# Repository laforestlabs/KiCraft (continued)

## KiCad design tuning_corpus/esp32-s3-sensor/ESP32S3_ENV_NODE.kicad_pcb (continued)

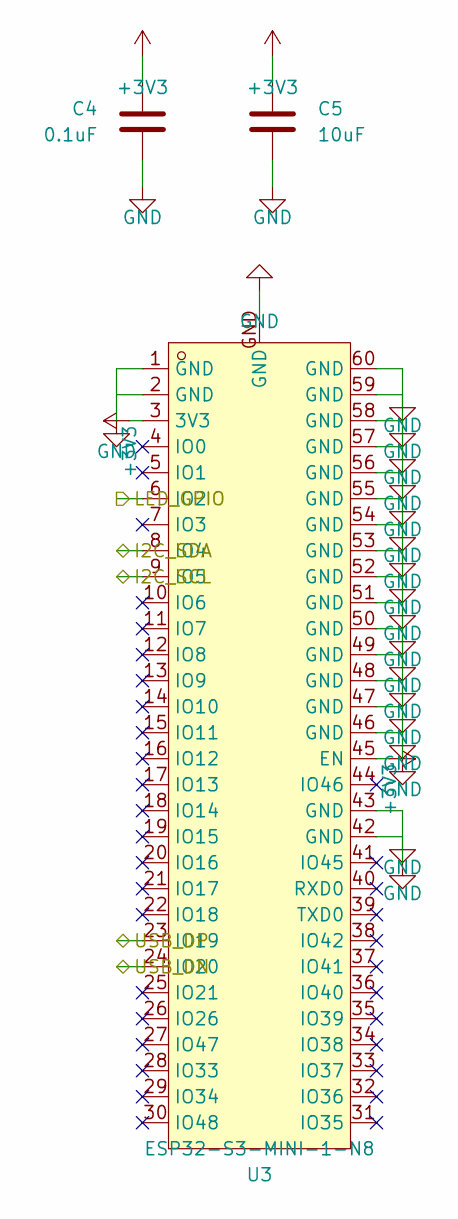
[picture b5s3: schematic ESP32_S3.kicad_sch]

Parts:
C4: 0.1uF; C_0805_2012Metric
C5: 10uF; C_0805_2012Metric
U3: ESP32-S3-MINI-1-N8; BULETM-SMD_ESP32-S3-MINI-1-N8

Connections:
+3V3: C4.1, C5.1, U3.3 (3V3), U3.45 (EN); also elsewhere on the board
I2C_SCL: U3.9 (IO5); also elsewhere on the board
I2C_SDA: U3.8 (IO4); also elsewhere on the board
LED_GPIO: U3.6 (IO2); also elsewhere on the board
USB_DN: U3.24 (IO20); also elsewhere on the board
USB_DP: U3.23 (IO19); also elsewhere on the board

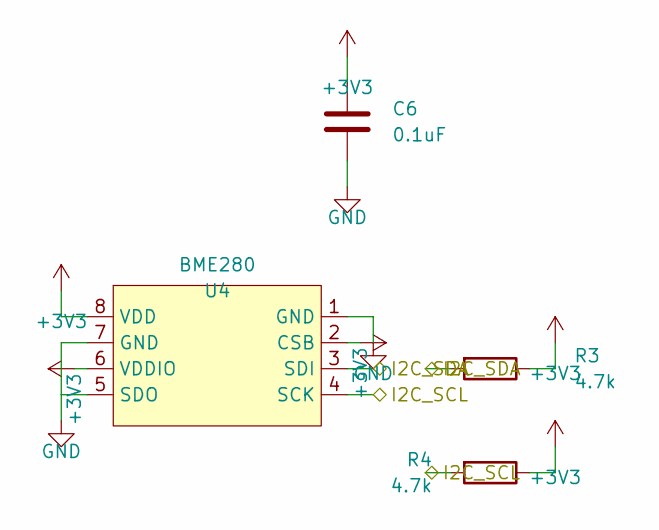
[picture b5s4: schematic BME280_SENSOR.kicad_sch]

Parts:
C6: 0.1uF; C_0805_2012Metric
R3, R4: 4.7k; R_0805_2012Metric
U4: BME280; LGA-8_BME280_BL

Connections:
+3V3: C6.1, R3.1, R4.1, U4.2 (CSB), U4.6 (VDDIO), U4.8 (VDD); also elsewhere on the board
I2C_SCL: R4.2, U4.4 (SCK); also elsewhere on the board
I2C_SDA: R3.2, U4.3 (SDI); also elsewhere on the board

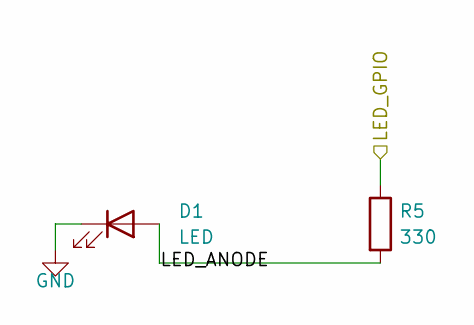
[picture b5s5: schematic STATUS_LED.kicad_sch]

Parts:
D1: LED; LED_0805_2012Metric
R5: 330; R_0805_2012Metric

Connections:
LED_ANODE: D1.2 (A), R5.2
LED_GPIO: R5.1; also elsewhere on the board

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
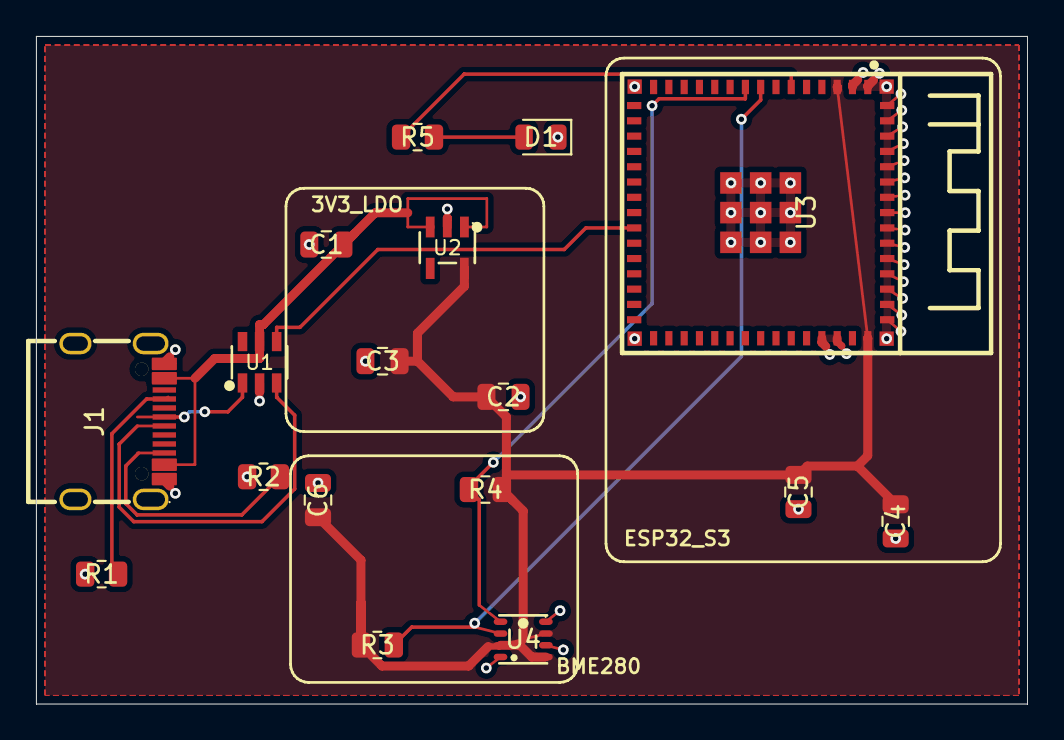
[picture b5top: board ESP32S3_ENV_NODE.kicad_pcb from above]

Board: 2 copper layers, 55.1 x 37.1 mm, 17 parts (0 on the bottom side), 13 nets.

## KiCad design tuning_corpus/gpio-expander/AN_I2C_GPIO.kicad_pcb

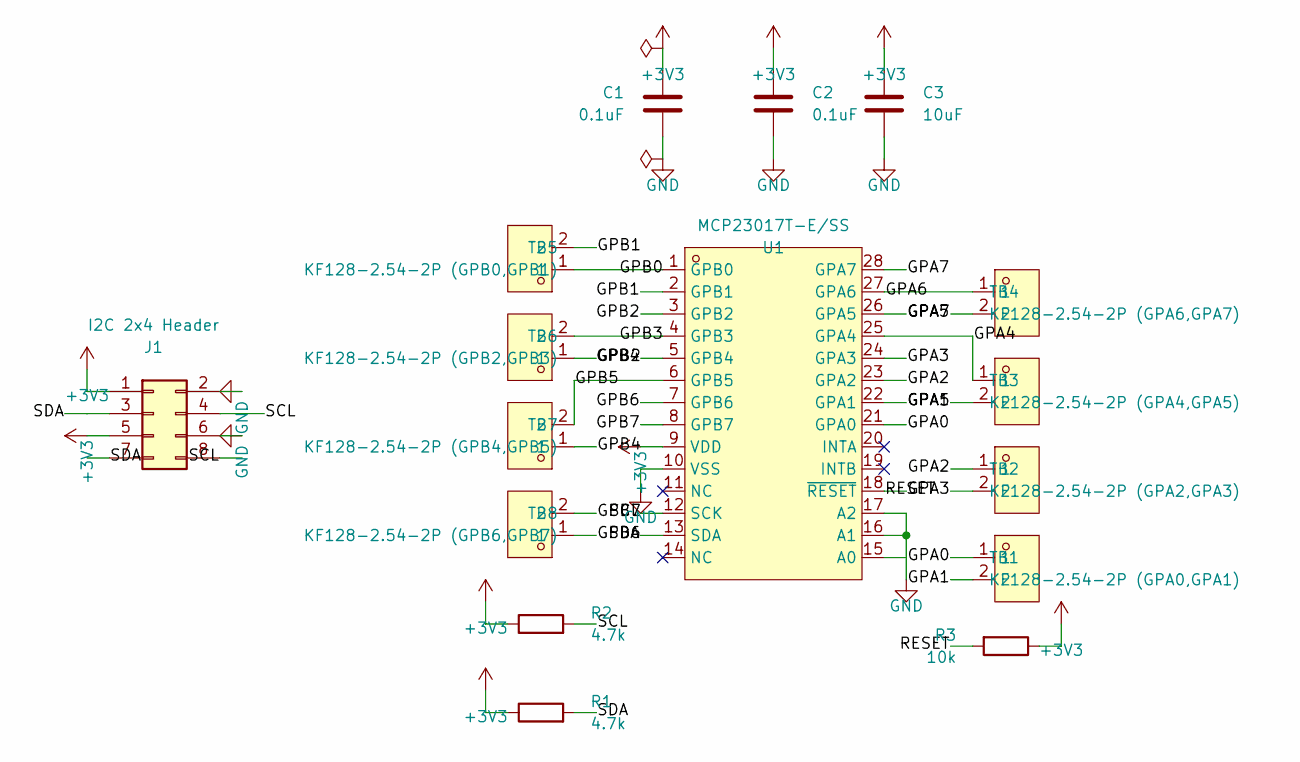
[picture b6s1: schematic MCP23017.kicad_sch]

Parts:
C1, C2: 0.1uF; C_0805_2012Metric
C3: 10uF; C_0805_2012Metric
J1: I2C 2x4 Header; PinHeader_2x04_P2.54mm_Vertical
R1, R2: 4.7k; R_0805_2012Metric
R3: 10k; R_0805_2012Metric
TB1: KF128-2.54-2P (GPA0,GPA1); CONN-TH_P2.54_KF128-2.54-2P
TB2: KF128-2.54-2P (GPA2,GPA3); CONN-TH_P2.54_KF128-2.54-2P
TB3: KF128-2.54-2P (GPA4,GPA5); CONN-TH_P2.54_KF128-2.54-2P
TB4: KF128-2.54-2P (GPA6,GPA7); CONN-TH_P2.54_KF128-2.54-2P
TB5: KF128-2.54-2P (GPB0,GPB1); CONN-TH_P2.54_KF128-2.54-2P
TB6: KF128-2.54-2P (GPB2,GPB3); CONN-TH_P2.54_KF128-2.54-2P
TB7: KF128-2.54-2P (GPB4,GPB5); CONN-TH_P2.54_KF128-2.54-2P
TB8: KF128-2.54-2P (GPB6,GPB7); CONN-TH_P2.54_KF128-2.54-2P
U1: MCP23017T-E/SS; SSOP-28_L10.2-W5.3-P0.65-LS7.8-BL

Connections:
GPA0: TB1.1, U1.21 (GPA0)
GPA1: TB1.2, U1.22 (GPA1)
GPA2: TB2.1, U1.23 (GPA2)
GPA3: TB2.2, U1.24 (GPA3)
GPA4: TB3.1, U1.25 (GPA4)
GPA5: TB3.2, U1.26 (GPA5)
GPA6: TB4.1, U1.27 (GPA6)
GPA7: TB4.2, U1.28 (GPA7)
GPB0: TB5.1, U1.1 (GPB0)
GPB1: TB5.2, U1.2 (GPB1)
GPB2: TB6.1, U1.3 (GPB2)
GPB3: TB6.2, U1.4 (GPB3)
GPB4: TB7.1, U1.5 (GPB4)
GPB5: TB7.2, U1.6 (GPB5)
GPB6: TB8.1, U1.7 (GPB6)
GPB7: TB8.2, U1.8 (GPB7)
RESET: R3.2, U1.18 (~RESET)
SCL: J1.4, J1.8, R2.2, U1.12 (SCK)
SDA: J1.3, J1.7, R1.2, U1.13 (SDA)

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
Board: 2 copper layers, 16 parts (0 on the bottom side), 21 nets, no tracks yet.

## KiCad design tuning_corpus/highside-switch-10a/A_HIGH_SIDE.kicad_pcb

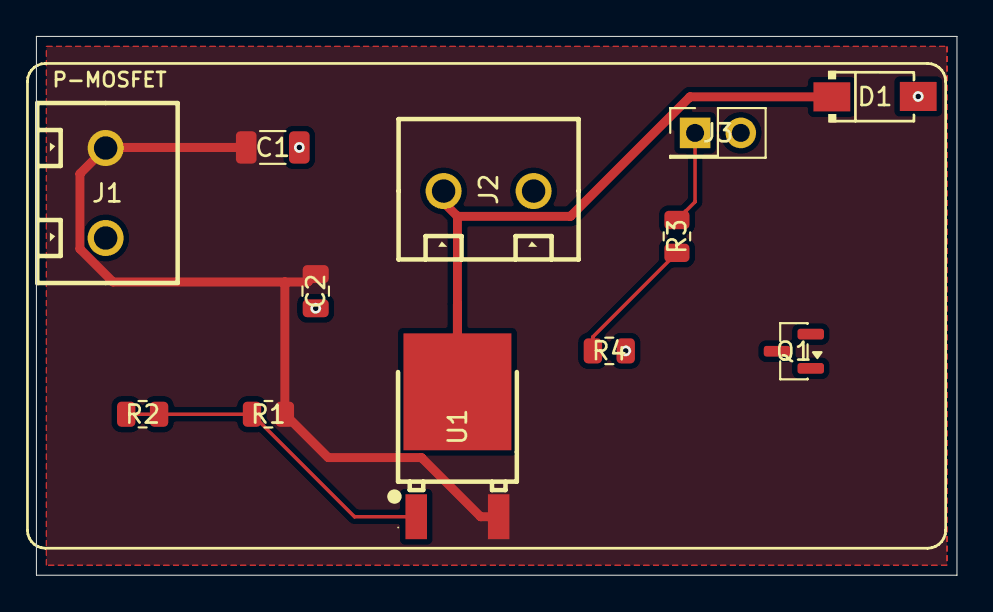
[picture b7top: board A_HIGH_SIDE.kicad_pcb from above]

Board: 2 copper layers, 51.1 x 29.9 mm, 12 parts (0 on the bottom side), 6 nets.

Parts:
C1: 10ÂµF; C_1206_3216Metric
C2: 0.1ÂµF; C_0805_2012Metric
D1: SS14; SMA_L4.3-W2.6-LS5.0-RD
J1, J2: 2-pin 5mm; CONN-TH_WJ126V-5.0-2P
J3: 2-pin 2.54mm; PinHeader_2x01_P2.54mm_Vertical
Q1: MMBT3904; SOT-23
R1, R3, R4: 10k; R_0805_2012Metric
R2: 1k; R_0805_2012Metric
U1: AOD4185; TO-252-3_L6.6-W6.1-P4.57-LS9.9-BR-CW

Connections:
BASE_DRV: R3.1, R4.1
ENABLE: J3.1, R3.2
GATE_DRV: R1.2, R2.1, R2.2, U1.1
GND: C1.2, C2.2, D1.2, J1.2, J2.2, J3.2, R4.2
VIN: C1.1, C2.1, J1.1, R1.1, U1.3
VOUT: D1.1, J2.1, U1.2
